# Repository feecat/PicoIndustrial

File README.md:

# PicoIndustrial
Industrial Control Module Based on RPI PICO  
----------  
  
You can [buy it at here](https://item.taobao.com/item.htm?id=641338698393), for now im in small batch production. Also you can manufactory it by yourself.  
There have 8 digital input, 8 relay output, 2 analog input, 2 analog output and 4 pico pin output.  
Digital IO is DC 24v PNP/NPN compatible, Analog IO is 0-10v or 0-20mA selectable.  
It was a simple plc or simple controller, Like some they called "arduino plc" controller but more powerfull.  
Here is product images, Actually its first that one-shoot successful product for me:  

## Example MicroPython Code  
```python
# Example of PicoIndustrial
from machine import Pin, PWM, ADC
from utime import sleep_ms
# Digital I/O Mapping
DI = [Pin(26, Pin.IN, Pin.PULL_DOWN), Pin(22, Pin.IN, Pin.PULL_DOWN), Pin(21, Pin.IN, Pin.PULL_DOWN), Pin(20, Pin.IN, Pin.PULL_DOWN), Pin(19, Pin.IN, Pin.PULL_DOWN), Pin(18, Pin.IN, Pin.PULL_DOWN), Pin(17, Pin.IN, Pin.PULL_DOWN), Pin(16, Pin.IN, Pin.PULL_DOWN)]
DO = [Pin(7, Pin.OUT), Pin(9, Pin.OUT), Pin(10, Pin.OUT), Pin(11, Pin.OUT), Pin(12, Pin.OUT), Pin(13, Pin.OUT), Pin(14, Pin.OUT), Pin(15, Pin.OUT)]
LED = [Pin(25, Pin.OUT), Pin(8, Pin.OUT), Pin(4, Pin.OUT)]
# ADC + DAC, DAC Use PWM to control voltage
AI = [ADC(Pin(28)), ADC(Pin(27))]
AO = [PWM(Pin(5)), PWM(Pin(6))]
AO[0].freq(500000)
AO[1].freq(500000)
# Write Init code here
LED[0].value(1)
# Write Loop code here
while True:
    # Analog IO
    AO[0].duty_u16(32767)
    print(AI[0].read_u16())
    # LED Toggle
    LED[2].value(not LED[2].value())
    # Digital IO
    DO[0].value(DI[0].value())
    DO[1].value(not DI[1].value())
    DO[2].value(DI[2].value())
    # Sleep
    sleep_ms(100)
    
```

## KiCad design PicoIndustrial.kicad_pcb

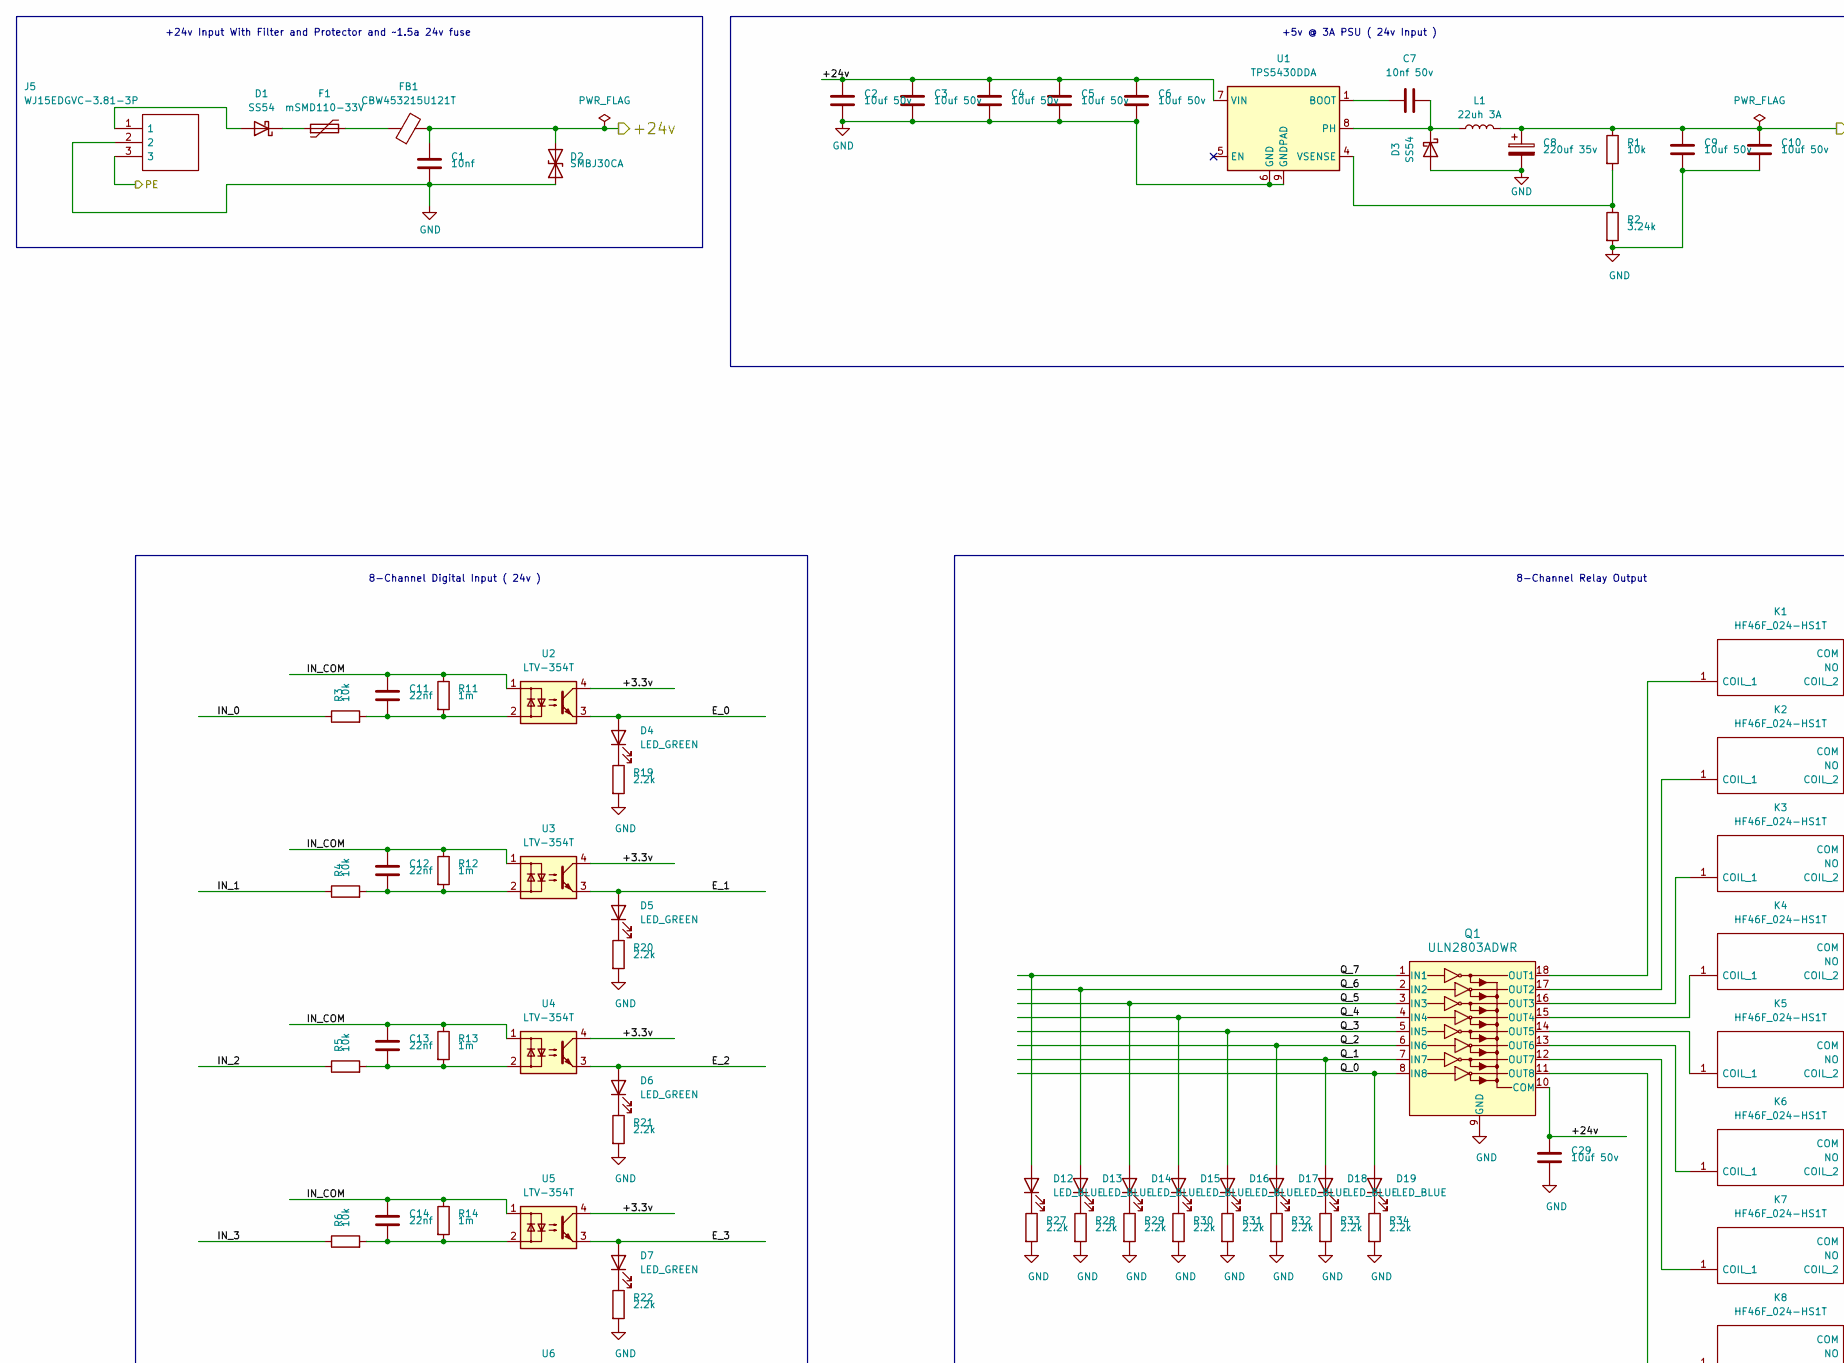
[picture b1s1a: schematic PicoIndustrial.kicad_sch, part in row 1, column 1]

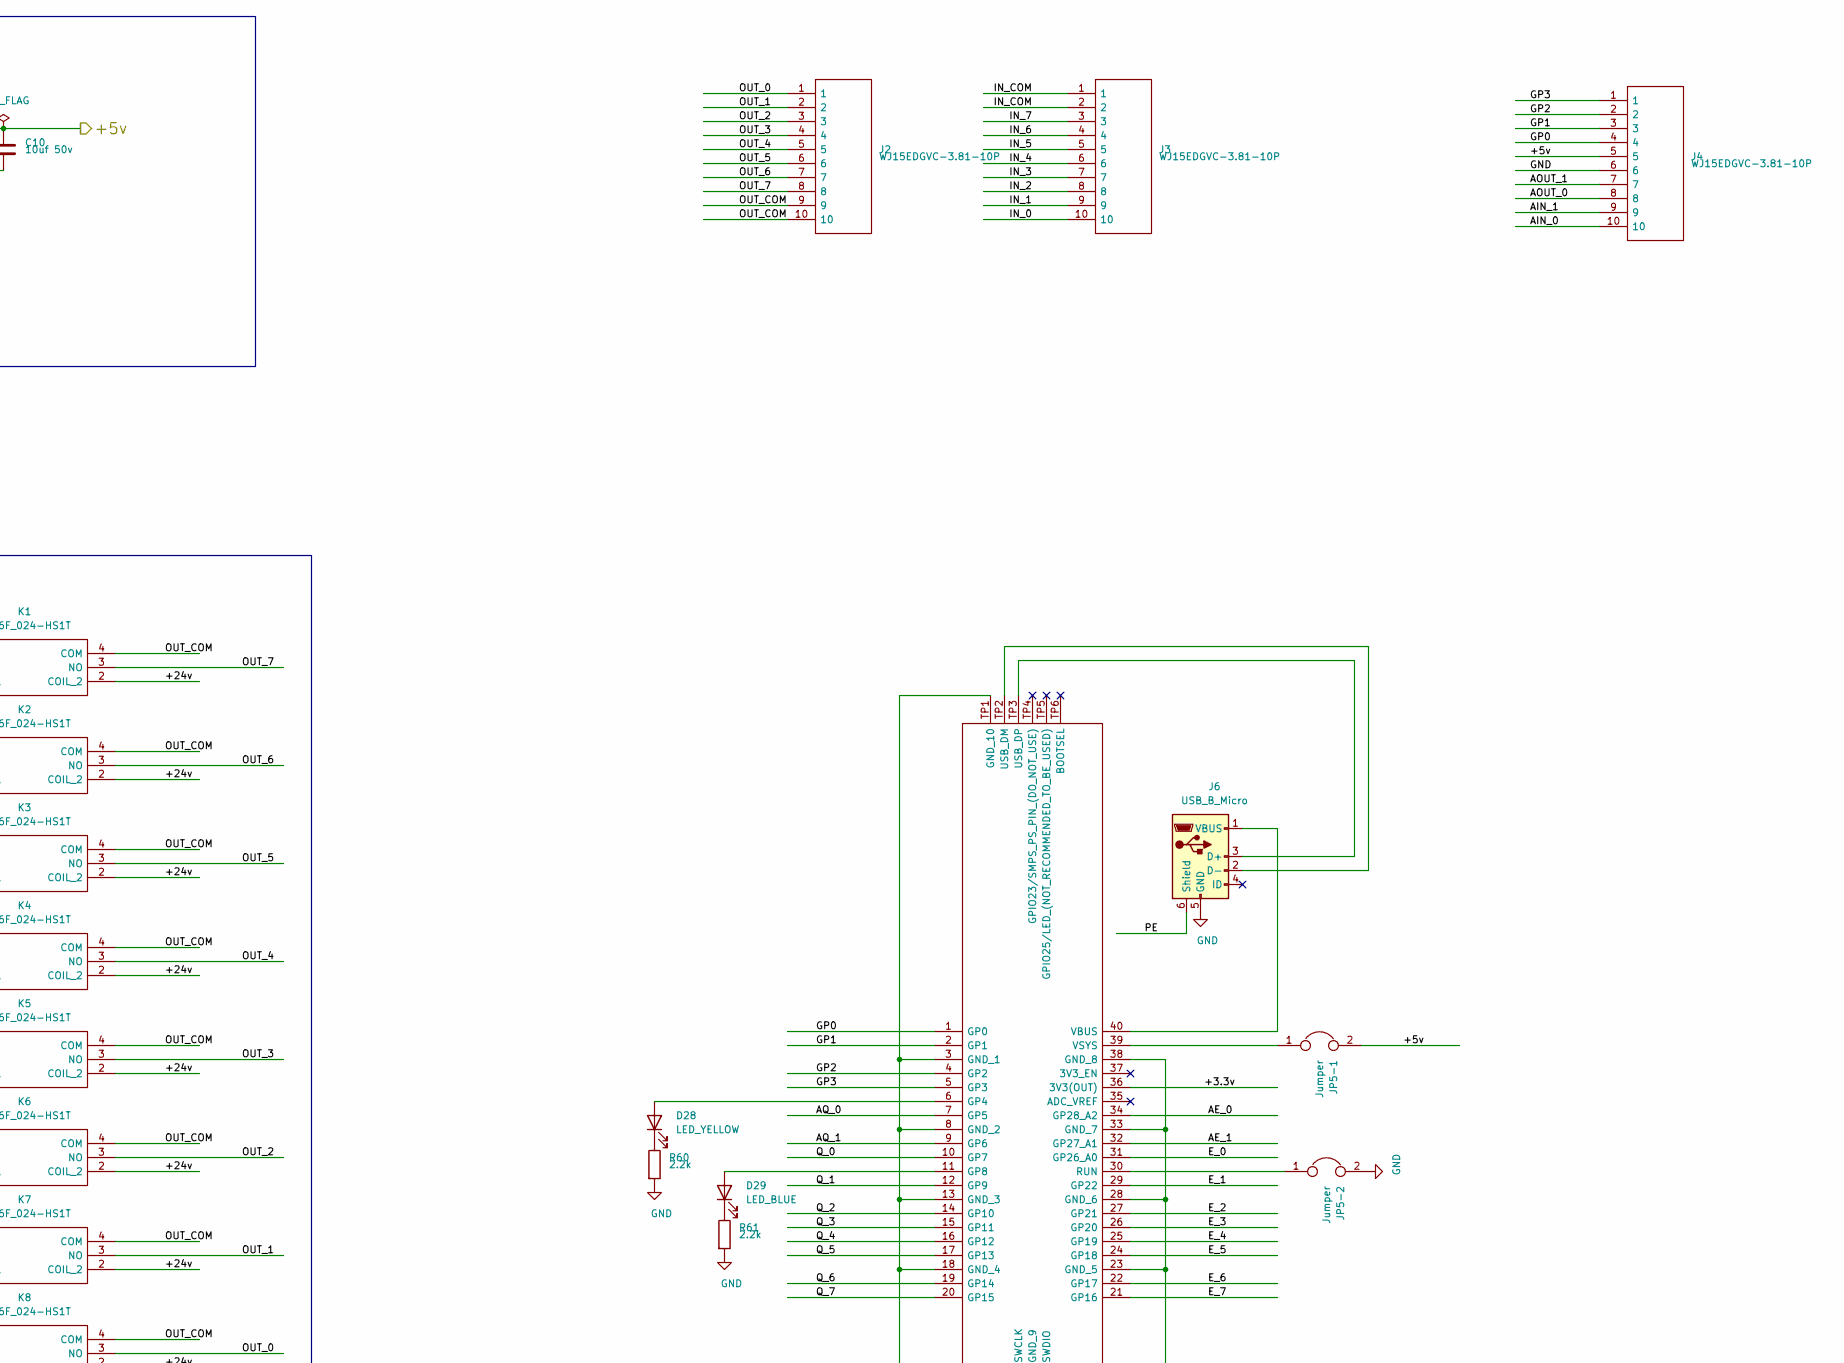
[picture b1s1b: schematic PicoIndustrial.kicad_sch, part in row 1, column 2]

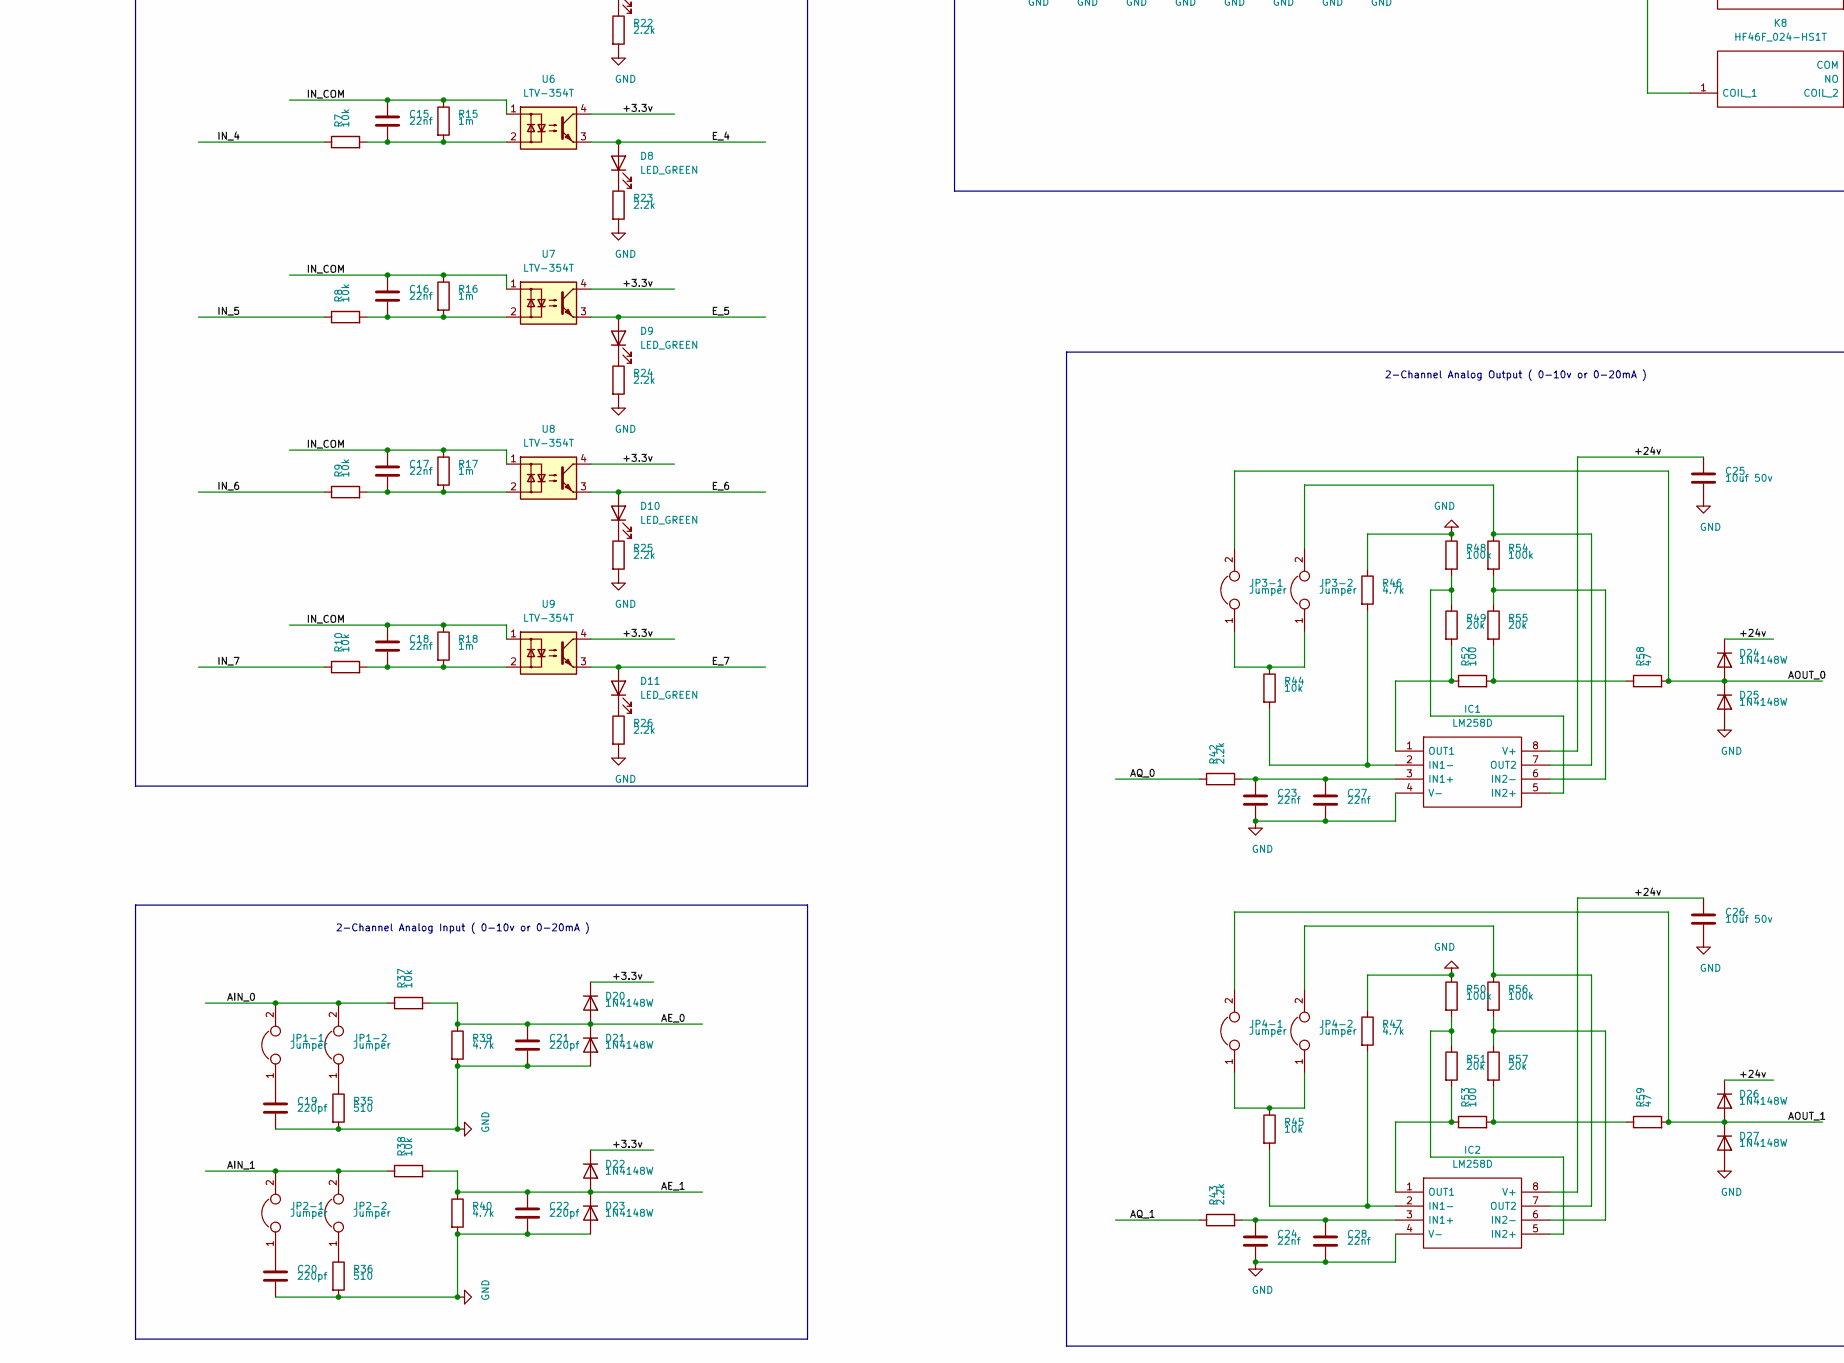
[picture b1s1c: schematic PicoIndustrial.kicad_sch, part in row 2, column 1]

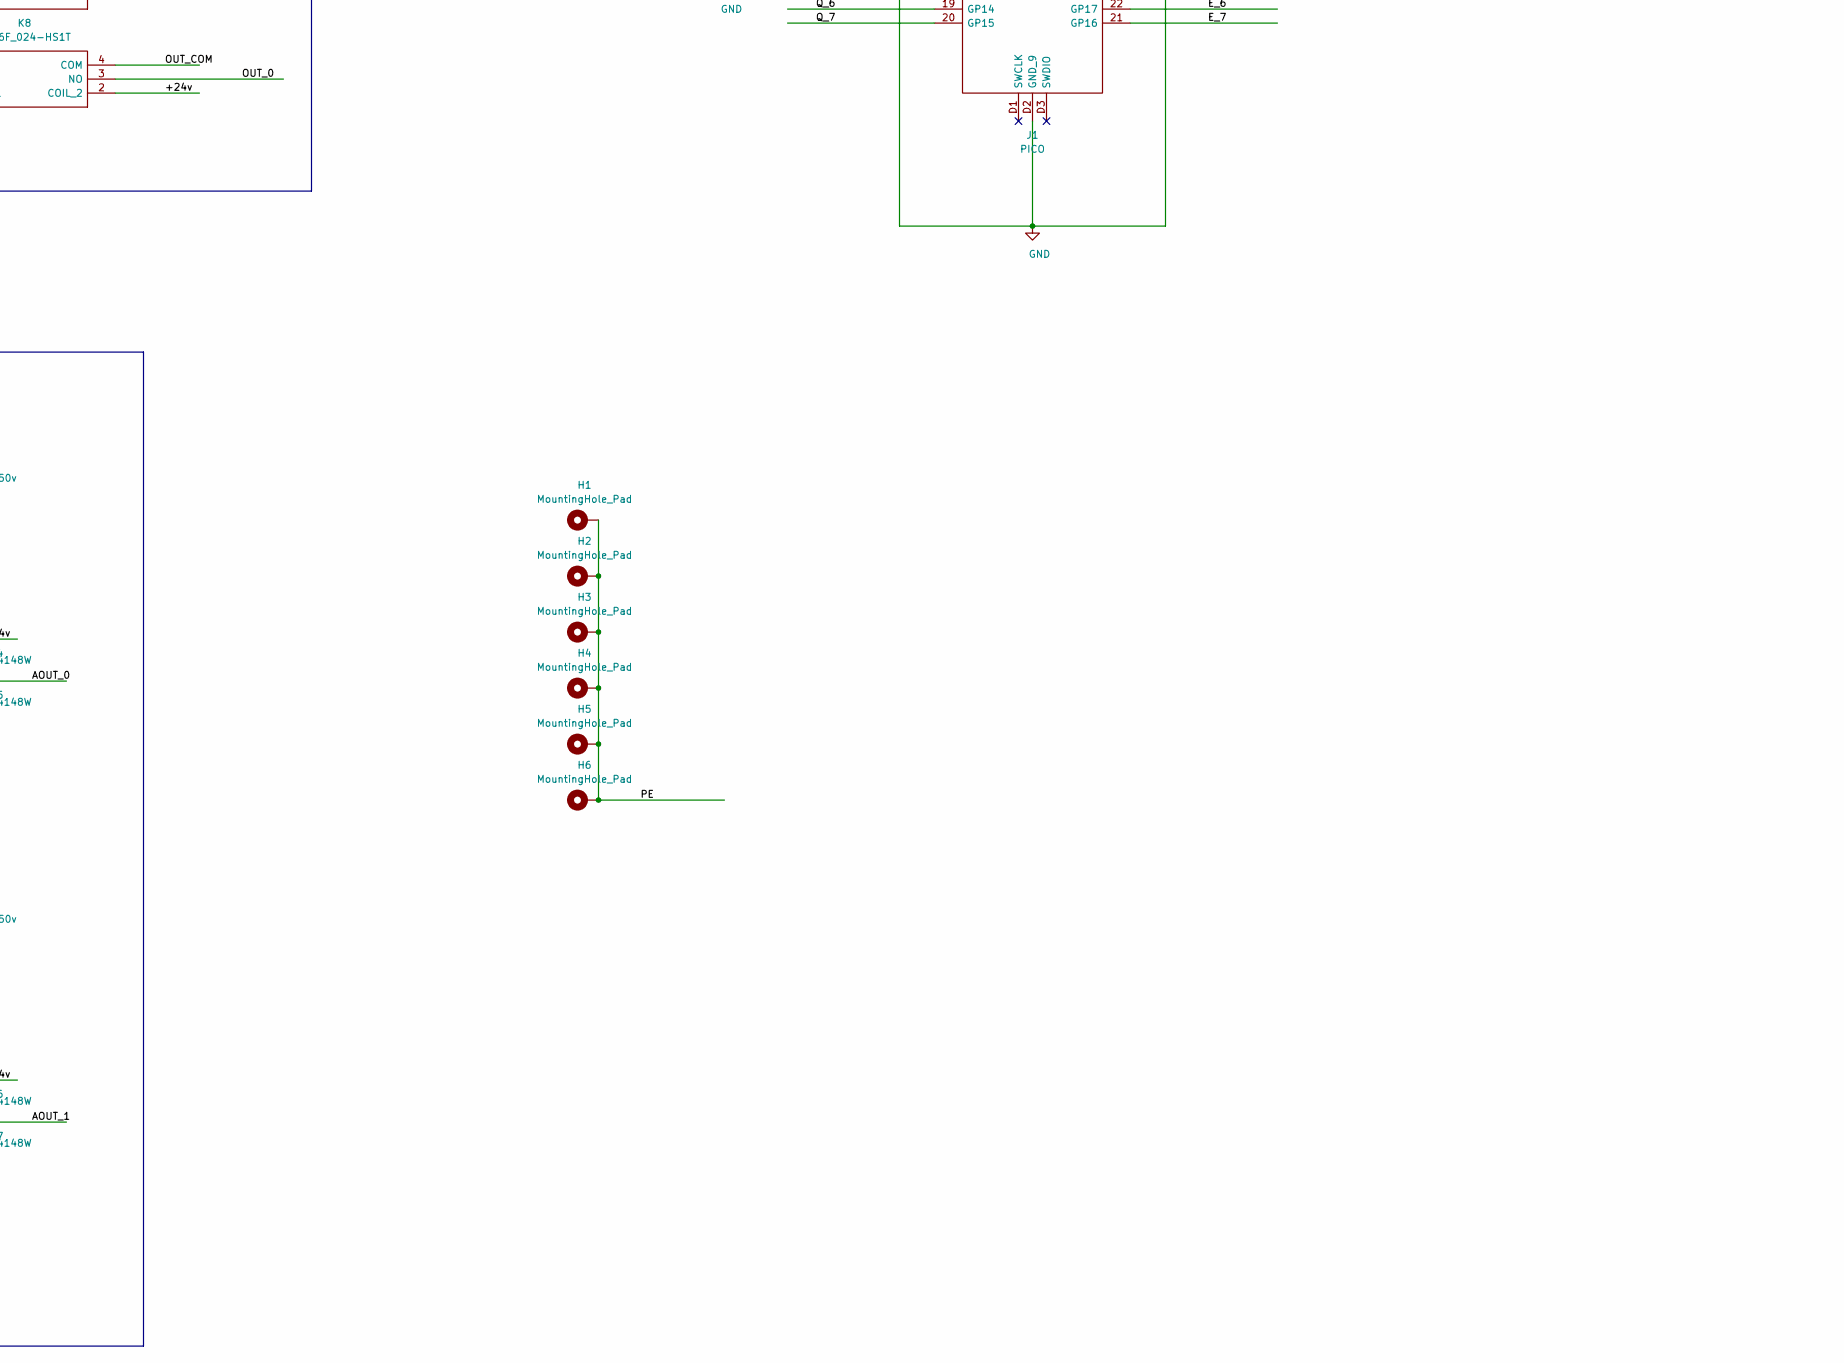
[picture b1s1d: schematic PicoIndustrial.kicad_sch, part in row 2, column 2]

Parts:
C1: 10nf; C_1812_4532Metric; MPN 1812B103K202NT
C2, C3, C4, C5, C6, C9, C10, C25, C26, C29: 10uf 50v; C_1206_3216Metric; MPN CL31A106KBHNNNE
C7: 10nf 50v; C_0603_1608Metric; MPN CL10B103KB8NNNC
C8: 220uf 35v; CP_Elec_8x10; MPN VEH221M1VTR-0810
C11, C12, C13, C14, C15, C16, C17, C18, C23, C24, C27, C28: 22nf; C_0603_1608Metric; MPN CL10B223KB8NNNC
C19, C20, C21, C22: 220pf; C_0603_1608Metric; MPN CL10B221KB8NNNC
D1, D3: SS54; D_SMA; MPN SS54
D2: SMBJ30CA; D_SMB; MPN SMBJ30CA
D4, D5, D6, D7, D8, D9, D10, D11: LED_GREEN; LED_0603_1608Metric; MPN 19-217/GHC-YR1S2/3T
D12, D13, D14, D15, D16, D17, D18, D19, D29: LED_BLUE; LED_0603_1608Metric; MPN 19-217/BHC-ZL1M2RY/3T
D20, D21, D22, D23, D24, D25, D26, D27: 1N4148W; D_SOD-123; MPN 1N4148W
D28: LED_YELLOW; LED_0603_1608Metric; MPN 19-213/Y2C-CQ2R2L/3T(CY)
F1: mSMD110-33V; Fuse_1812_4532Metric; MPN mSMD110-33V
FB1: CBW453215U121T; L_1812_4532Metric; MPN CBW453215U121T
H1, H2, H3, H4, H5, H6: MountingHole_Pad; MountingHole_3.2mm_M3_Pad_Via
IC1, IC2: LM258D; SOIC127P600X175-8N; MPN LM258DR
J1: PICO; PICO_HOLE; MPN Pico
J2, J3, J4: WJ15EDGVC-3.81-10P; SHDR10W85P0X381_1X10_3898X700X935P; MPN WJ15EDGVC-3.81-10P
J5: WJ15EDGVC-3.81-3P; SHDR12W85P0X381_1X3_4660X700X935P; MPN WJ15EDGVM-3.81-3P
J6: USB_B_Micro; USB_Micro-B_Wuerth_614105150721_Vertical; MPN MICRO 180°JB
JP1-1, JP1-2, JP2-1, JP2-2, JP3-1, JP3-2, JP4-1, JP4-2, JP5-1, JP5-2: Jumper; TestPoint_2Pads_Pitch2.54mm_Drill0.8mm
K1, K2, K3, K4, K5, K6, K7, K8: HF46F_024-HS1T; HF46F024HS1T; MPN HF46F/24-HS1
L1: 22uh 3A; L_12x12mm_H6mm; MPN SLH1207S220MTT
Q1: ULN2803ADWR; SOIC-18W_7.5x11.6mm_P1.27mm
R1, R3, R4, R5, R6, R7, R8, R9, R10, R37, R38, R44, R45: 10k; R_0603_1608Metric; MPN 0603WAF1002T5E
R2: 3.24k; R_0603_1608Metric; MPN 0603WAF3241T5E
R11, R12, R13, R14, R15, R16, R17, R18: 1m; R_0603_1608Metric; MPN 0603WAF1004T5E
R19, R20, R21, R22, R23, R24, R25, R26, R27, R28, R29, R30, R31, R32, R33, R34, R42, R43, R60, R61: 2.2k; R_0603_1608Metric; MPN 0603WAF2201T5E
R35, R36: 510; R_1206_3216Metric; MPN 1206W4F5100T5E
R39, R40, R46, R47: 4.7k; R_0603_1608Metric; MPN 0603WAF4701T5E
R48, R50, R54, R56: 100k; R_0603_1608Metric; MPN 0603WAF1003T5E
R49, R51, R55, R57: 20k; R_0603_1608Metric; MPN 0603WAF2002T5E
R52, R53: 100; R_0603_1608Metric; MPN 0603WAF1000T5E
R58, R59: 47; R_0603_1608Metric; MPN 0603WAF470JT5E
U1: TPS5430DDA; TI_SO-PowerPAD-8_ThermalVias; MPN TPS5430DDAR
U2, U3, U4, U5, U6, U7, U8, U9: LTV-354T; SO-4_4.4x3.6mm_P2.54mm; MPN LTV-354T

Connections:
/+3.3v: D20.1 (K), D22.1 (K), J1.36 (3V3(OUT)), U2.4, U3.4, U4.4, U5.4, U6.4, U7.4, U8.4, U9.4
/+5v: C8.1, C9.1, C10.1, J4.5, JP5-1.2, L1.2, R1.1
/+24v: C1.1, C2.1, C3.1, C4.1, C5.1, C6.1, C25.1, C26.1, C29.1, D2.2 (A2), D24.1 (K), D26.1 (K), FB1.2, IC1.8 (V+), IC2.8 (V+), K1.2 (COIL_2), K2.2 (COIL_2), K3.2 (COIL_2), K4.2 (COIL_2), K5.2 (COIL_2), K6.2 (COIL_2), K7.2 (COIL_2), K8.2 (COIL_2), Q1.10 (COM), U1.7 (VIN)
/AE_0: C21.2, D20.2 (A), D21.1 (K), J1.34 (GP28_A2), R37.2, R39.1
/AE_1: C22.2, D22.2 (A), D23.1 (K), J1.32 (GP27_A1), R38.2, R40.1
/AIN_0: J4.10, JP1-1.2, JP1-2.2, R37.1
/AIN_1: J4.9, JP2-1.2, JP2-2.2, R38.1
/AOUT_0: D24.2 (A), D25.1 (K), J4.8, JP3-1.2, R58.2
/AOUT_1: D26.2 (A), D27.1 (K), J4.7, JP4-1.2, R59.2
/AQ_0: J1.7 (GP5), R42.1
/AQ_1: J1.9 (GP6), R43.1
/E_0: D4.2 (A), J1.31 (GP26_A0), U2.3
/E_1: D5.2 (A), J1.29 (GP22), U3.3
/E_2: D6.2 (A), J1.27 (GP21), U4.3
/E_3: D7.2 (A), J1.26 (GP20), U5.3
/E_4: D8.2 (A), J1.25 (GP19), U6.3
/E_5: D9.2 (A), J1.24 (GP18), U7.3
/E_6: D10.2 (A), J1.22 (GP17), U8.3
/E_7: D11.2 (A), J1.21 (GP16), U9.3
/GP0: J1.1 (GP0), J4.4
/GP1: J1.2 (GP1), J4.3
/GP2: J1.4 (GP2), J4.2
/GP3: J1.5 (GP3), J4.1
/IN_0: J3.10, R3.1
/IN_1: J3.9, R4.1
/IN_2: J3.8, R5.1
/IN_3: J3.7, R6.1
/IN_4: J3.6, R7.1
/IN_5: J3.5, R8.1
/IN_6: J3.4, R9.1
/IN_7: J3.3, R10.1
/IN_COM: C11.2, C12.2, C13.2, C14.2, C15.2, C16.2, C17.2, C18.2, J3.1, J3.2, R11.1, R12.1, R13.1, R14.1, R15.1, R16.1, R17.1, R18.1, U2.1, U3.1, U4.1, U5.1, U6.1, U7.1, U8.1, U9.1
/OUT_0: J2.1, K8.3 (NO)
/OUT_1: J2.2, K7.3 (NO)
/OUT_2: J2.3, K6.3 (NO)
/OUT_3: J2.4, K5.3 (NO)
/OUT_4: J2.5, K4.3 (NO)
/OUT_5: J2.6, K3.3 (NO)
/OUT_6: J2.7, K2.3 (NO)
/OUT_7: J2.8, K1.3 (NO)
/OUT_COM: J2.9, J2.10, K1.4 (COM), K2.4 (COM), K3.4 (COM), K4.4 (COM), K5.4 (COM), K6.4 (COM), K7.4 (COM), K8.4 (COM)
/PE: H1.1, H2.1, H3.1, H4.1, H5.1, H6.1, J5.3, J6.6 (Shield)
/Q_0: D19.2 (A), J1.10 (GP7), Q1.8 (IN8)
/Q_1: D18.2 (A), J1.12 (GP9), Q1.7 (IN7)
/Q_2: D17.2 (A), J1.14 (GP10), Q1.6 (IN6)
/Q_3: D16.2 (A), J1.15 (GP11), Q1.5 (IN5)
/Q_4: D15.2 (A), J1.16 (GP12), Q1.4 (IN4)
/Q_5: D14.2 (A), J1.17 (GP13), Q1.3 (IN3)
/Q_6: D13.2 (A), J1.19 (GP14), Q1.2 (IN2)
/Q_7: D12.2 (A), J1.20 (GP15), Q1.1 (IN1)
GND: C1.2, C2.2, C3.2, C4.2, C5.2, C6.2, C8.2, C9.2, C10.2, C19.1, C20.1, C21.1, C22.1, C23.1, C24.1, C25.2, C26.2, C27.1, C28.1, C29.2, D2.1 (A1), D3.2 (A), D21.2 (A), D23.2 (A), D25.2 (A), D27.2 (A), IC1.4 (V-), IC2.4 (V-), J1.3 (GND_1), J1.8 (GND_2), J1.13 (GND_3), J1.18 (GND_4), J1.23 (GND_5), J1.28 (GND_6), J1.33 (GND_7), J1.38 (GND_8), J1.D2 (GND_9), J1.TP1 (GND_10), J4.6, J5.2, J6.5 (GND), JP5-2.2, Q1.9 (GND), R2.2, R19.2, R20.2, R21.2, R22.2, R23.2, R24.2, R25.2, R26.2, R27.2, R28.2, R29.2, R30.2, R31.2, R32.2, R33.2, R34.2, R35.2, R36.2, R39.2, R40.2, R46.1, R47.1, R48.1, R50.1, R60.2, R61.2, U1.6 (GND), U1.9 (GNDPAD)
unnamed: C7.1, U1.1 (BOOT)
unnamed: C7.2, D3.1 (K), L1.1, U1.8 (PH)
unnamed: C11.1, R3.2, R11.2, U2.2
unnamed: C12.1, R4.2, R12.2, U3.2
unnamed: C13.1, R5.2, R13.2, U4.2
unnamed: C14.1, R6.2, R14.2, U5.2
unnamed: C15.1, R7.2, R15.2, U6.2
unnamed: C16.1, R8.2, R16.2, U7.2
unnamed: C17.1, R9.2, R17.2, U8.2
unnamed: C18.1, R10.2, R18.2, U9.2
unnamed: C19.2, JP1-1.1
unnamed: C20.2, JP2-1.1
unnamed: C23.2, C27.2, IC1.3 (IN1+), R42.2
unnamed: C24.2, C28.2, IC2.3 (IN1+), R43.2
unnamed: D1.1 (K), F1.1
unnamed: D1.2 (A), J5.1
unnamed: D4.1 (K), R19.1
unnamed: D5.1 (K), R20.1
unnamed: D6.1 (K), R21.1
unnamed: D7.1 (K), R22.1
unnamed: D8.1 (K), R23.1
unnamed: D9.1 (K), R24.1
unnamed: D10.1 (K), R25.1
unnamed: D11.1 (K), R26.1
unnamed: D12.1 (K), R27.1
unnamed: D13.1 (K), R28.1
unnamed: D14.1 (K), R29.1
unnamed: D15.1 (K), R30.1
unnamed: D16.1 (K), R31.1
unnamed: D17.1 (K), R32.1
unnamed: D18.1 (K), R33.1
unnamed: D19.1 (K), R34.1
unnamed: D28.1 (K), R60.1
unnamed: D28.2 (A), J1.6 (GP4)
unnamed: D29.1 (K), R61.1
unnamed: D29.2 (A), J1.11 (GP8)
unnamed: F1.2, FB1.1
unnamed: IC1.1 (OUT1), R49.2, R52.1
unnamed: IC1.2 (IN1-), R44.2, R46.2
unnamed: IC1.5 (IN2+), R48.2, R49.1
unnamed: IC1.6 (IN2-), R54.2, R55.1
unnamed: IC1.7 (OUT2), JP3-2.2, R54.1
unnamed: IC2.1 (OUT1), R51.2, R53.1
unnamed: IC2.2 (IN1-), R45.2, R47.2
unnamed: IC2.5 (IN2+), R50.2, R51.1
unnamed: IC2.6 (IN2-), R56.2, R57.1
unnamed: IC2.7 (OUT2), JP4-2.2, R56.1
unnamed: J1.30 (RUN), JP5-2.1
unnamed: J1.39 (VSYS), JP5-1.1
unnamed: J1.40 (VBUS), J6.1 (VBUS)
unnamed: J1.TP2 (USB_DM), J6.2 (D-)
unnamed: J1.TP3 (USB_DP), J6.3 (D+)
unnamed: JP1-2.1, R35.1
unnamed: JP2-2.1, R36.1
unnamed: JP3-1.1, JP3-2.1, R44.1
unnamed: JP4-1.1, JP4-2.1, R45.1
unnamed: K1.1 (COIL_1), Q1.18 (OUT1)
unnamed: K2.1 (COIL_1), Q1.17 (OUT2)
unnamed: K3.1 (COIL_1), Q1.16 (OUT3)
unnamed: K4.1 (COIL_1), Q1.15 (OUT4)
unnamed: K5.1 (COIL_1), Q1.14 (OUT5)
unnamed: K6.1 (COIL_1), Q1.13 (OUT6)
unnamed: K7.1 (COIL_1), Q1.12 (OUT7)
unnamed: K8.1 (COIL_1), Q1.11 (OUT8)
unnamed: R1.2, R2.1, U1.4 (VSENSE)
unnamed: R52.2, R55.2, R58.1
unnamed: R53.2, R57.2, R59.1

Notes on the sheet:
+24v Input With Filter and Protector and ~~1.5a 24v fuse
8-Channel Digital Input ( 24v )
2-Channel Analog Input ( 0-10v or 0-20mA )
+5v @ 3A PSU ( 24v Input )
8-Channel Relay Output
2-Channel Analog Output ( 0-10v or 0-20mA )

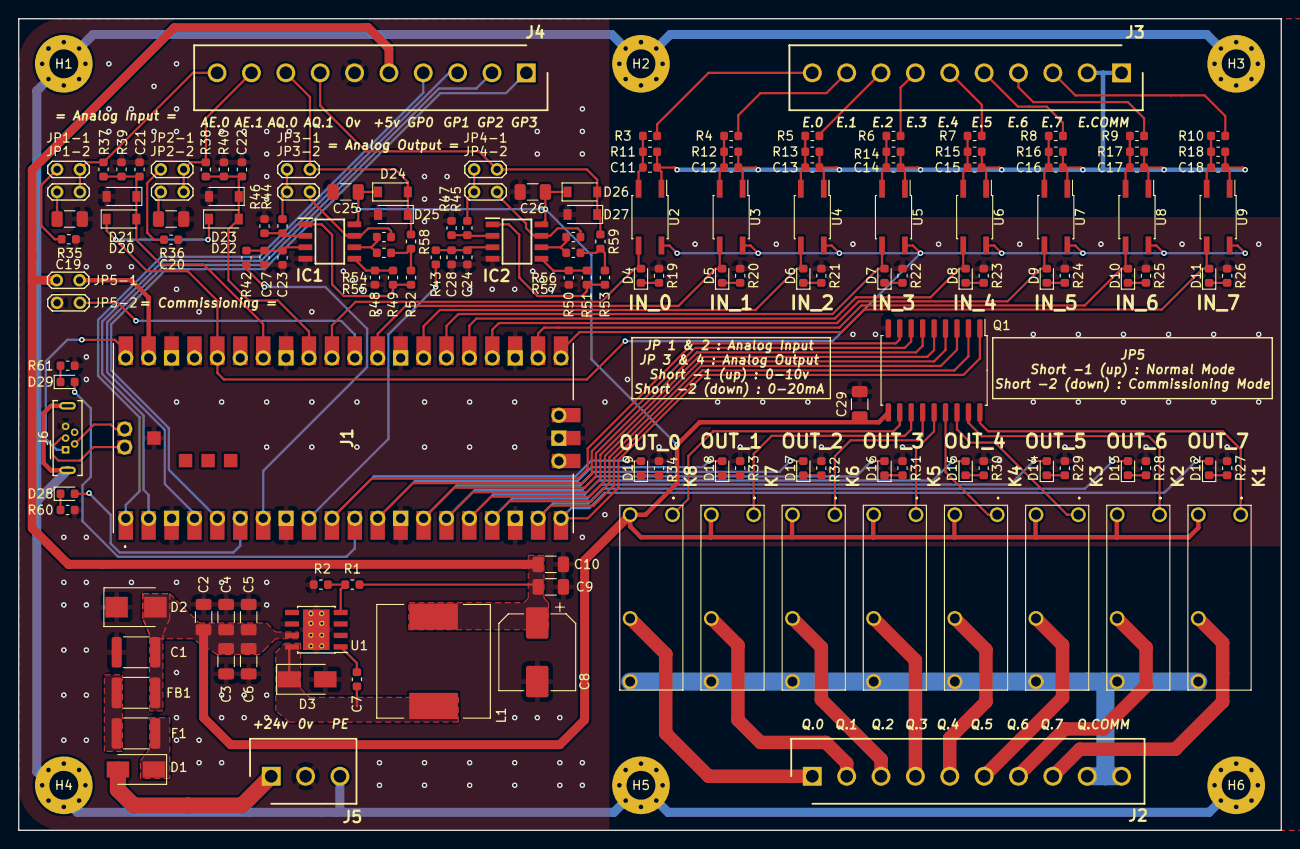
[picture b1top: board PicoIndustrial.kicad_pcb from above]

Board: 2 copper layers, 140.0 x 90.0 mm, 163 parts (0 on the bottom side), 118 nets.

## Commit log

2021-03-18 Upload Images
2021-03-18 Update 3d modules
2021-03-27 no update
2021-03-27 Update Images
